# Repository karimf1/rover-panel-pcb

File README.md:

# rover-panel-pcb 

The PCB was missing. It sits on
four standoffs on the panel plate, between the shunt and the signal
connector, and does three jobs:

- **precharge** — it switches the pack through the panel's 22 Ω resistor `R1`
  into the ESC bank, and holds contactor `K1` open until the switched bus
  reaches ~90 % of the pack
- **interlock** — `K1`'s coil is energised through the E-stop loop *and* this
  board, so the board can open `K1` but nothing on it can close `K1` past an
  open E-stop
- **current sense** — an INA228 on the panel's 0.75 mΩ shunt `RS1`, reported
  over I2C

It replaces two of the panel's bought parts — `K2`, an automotive precharge
relay, and `A1`, an INA228 breakout on standoffs — and it answers two of the
panel's open questions: *"precharge is sized by hand and is not in any check"*
and *"is the E-stop hard-wired in series with the contactor coil?"*

The one claim the board is built to prove:

> **K1 cannot close unless the E-stop loop is closed AND the host has raised a
> fresh ARM edge AND the switched bus has reached the precharge threshold** —
> and that is hardware, checked against the exported netlist, not a promise
> made by firmware. There is no firmware.

---

## 1. How the interlock works

The logic is four comparators, one AND gate and one D flip-flop. Every node
that feeds the interlock is an open-collector output pulled up **to EN, not to
5 V** — so the instant the board disarms, every one of them falls with it.

| signal | made by | means |
|---|---|---|
| `ESTOP_OK` | U3C: the *far* side of the E-stop loop (`COIL_POS`) above 13.7 V | the mushroom switch is closed |
| `ARM` | U3D: host line above 1.37 V, 100 k pull-down | the host asked; an unplugged harness reads as *no* |
| `CLR#` | U4: `ARM AND ESTOP_OK` | either one dropping clears the latch immediately |
| `EN` | U5 (74LVC1G74) Q, set only on a **rising edge** of `ARM` delayed 10 ms | armed |
| `CHG` | U3A: switched bus / always-on bus **below** the threshold | precharging |
| `FAULT` | U3B: `CHG` has been high longer than the timer (≥ 1.68 s) | the bus is not charging — latches |
| `K1_G` | `EN`, pulled low by `CHG` (Q2) or `FAULT` (Q3), 1 ms RC | close the contactor |
| `PRE_G` | `EN`, pulled low by `FAULT` (Q4) | precharge switch on |

The flip-flop is there for one reason. With a plain AND gate, releasing the
E-stop while the host is still asserting `ARM` would re-energise the drive
motors on its own. With the latch, **an E-stop release does nothing until the
host drops `ARM` and raises it again.** That is what competition rules mean by
a deliberate restart, and it is scenario 5 in the simulation below.

The K1 coil path is:

```
+24 V -> P1.8 -> J1 -> E-stop -> J1 -> P1.3 -> P1.4 -> K1 coil -> P1.6 -> Q1 -> GND
```

`Q1` is on the low side. It can only *interrupt* that loop.

## 2. The design numbers

### Precharge threshold: a window, not a number

The comparator does not measure "90 % of 24 V". It compares two dividers —
the switched bus against the always-on bus — so it holds from a 21 V cutoff
to a 29.4 V full pack. Its threshold still moves, for three reasons, and
`calcs.pre_ratio_window()` takes every corner of all three:

- the hysteresis resistor injects a fixed 5 V into a divider of a *varying*
  pack, so the trip point shifts with pack voltage
- the four ratio resistors. They are 0.1 % parts because with 1 % parts the highest
  corner trips at 94.75 %, which is **above** the 94.50 % the bus can reach. The
  board would fault on a low pack.
- the LM339's 5 mV offset plus its 250 nA bias current through each divider

```
precharge threshold window     88.34 .. 91.74 % of pack
bus can reach through R1       94.50 % at 21 V, with 50 mA of ESC idle draw
```

**The ESC idle draw is the constraint.** The bus charges towards
`V − I_idle × R1`, not towards `V`. At a 21 V pack and 50 mA of idle current,
R1 takes 1.1 V off the target, and a threshold set at the textbook 95 % would
never be reached — the board would fault on every power-up. The 50 mA is
assumed and is the first thing to measure (§6).

### The fault timer has to outlast a slow precharge

```
precharge time, nominal        0.41 s    (6 mF, 25.9 V)
precharge time, worst          0.73 s    (9 mF, 21 V, highest threshold)
fault timer                    1.68 / 2.36 / 2.66 s   (min / nom / max)
```

The minimum assumes the 10 µF X7R timing capacitor has lost 25 % to tolerance
and DC bias, and that the comparator's full bias current is helping to charge
it. That still leaves 2.3× margin over the slowest legitimate precharge. The
maximum is bounded too: into a dead short, `R1` sees 41 W, inside its 50 W
continuous rating, for as long as the timer takes.

### The panel's supply budget

The panel's `params.py` reserves a supply for the board: a 2 A time-lag fuse on
`DIN2-203`, 18 AWG, 0.2 A continuous and a 2.5 A peak. The panel's
`sizing.py` sizes the wiring from those numbers, and this board checks that
its worst case fits inside them. Neither side can quietly outgrow the other.

```
24 V draw                      76 mA continuous (70 mA of it is K1's hold current)
                               2.17 A worst instant: K1 pull-in while precharge still conducts
```

### Everything else

| check | result |
|---|---|
| INA228 full scale at `ADCRANGE = 0` | 218 A, 0.42 mA per count, `SHUNT_CAL` = 2803 |
| current error at 10 A | 0.31 % (shunt 0.25 %, INA228 gain, offset, filter bias) |
| input TVS SM6T36A | stands off 30.8 V > 29.4 V; clamps 49.9 V < 60 V (every FET on the 24 V side) |
| K1 FET gate drive | 4.85 V on a 5 V −2 % rail, ≥ the 4.5 V its RDS(on) is quoted at |
| K1 coil at pack cutoff | 19.8 V ≥ 16 V pickup, after the E-stop loop, the FET and panel wiring |
| precharge FET gate | zener-clamped, ≤ 12.6 V worst case, from 21 V to 29.4 V (fully on, under ±20 V) |
| every LM339 input | inside `VCC − 1.5 V` at a full pack |
| power traces | 1.0 mm vs 0.70 mm IPC-2221 at 2.5 A as if continuous |

### The behaviour, simulated

`test_calcs.py` finishes with a 1 ms-step simulation of the interlock built
from those same thresholds and time constants — nothing retuned for the test:

```
PASS  power-up, ARM low: nothing switches
PASS  ARM with a healthy bus (3 mF): precharge, then K1, no fault  -- K1 closes 0.20 s after ARM, bus at 90.7 %
PASS  ARM with a healthy bus (9 mF): precharge, then K1, no fault  -- K1 closes 0.58 s after ARM, bus at 90.7 %
PASS  ARM into a shorted bus: FAULT latches, precharge stops, K1 never closes  -- fault 2.36 s after ARM
PASS  E-stop opens while K1 is closed: K1 drops within 1 ms
PASS  E-stop released with ARM still high: K1 stays OPEN (needs a new ARM edge)
PASS  ARM cycled after the E-stop reset: precharge and K1 again
PASS  FAULT holds for as long as ARM stays high (a latch, not a retry loop)
PASS  dropping ARM clears FAULT and leaves everything off
```

## 3. What changed from the plan

1. **It had no latch.** The plan's logic was `ARM AND E-STOP AND PRECHARGED`.
   Writing scenario 4 of the simulation showed what that does: release the
   E-stop with `ARM` still high and the motors come back on by themselves.
   The 74LVC1G74 and its 10 ms clock delay are the fix. KiCad 9 ships no
   74LVC1G74 symbol, so it is generated from a pin map in `spec.py`
   (`hw/gen/gen_lib.py`).
2. **The supply fuse is 2 A, not 1 A.** A 1 A fuse passes the board's 76 mA,
   but K1's 2 A pull-in comes through the same fuse.
3. **No 3.3 V rail.** The plan had an LDO for the INA228. Everything runs at
   5 V instead. The INA228's I2C thresholds do not follow its supply, and
   every output to the host is an open-drain FET, so this 5 V board never
   drives a 3.3 V pin. (That INA228 fact is one of the seven items flagged
   `VERIFY`.)
4. **The board is 110 × 46 mm, not ~90 × 55.** The panel set its height:
   25 mm of signal clearance to `K1` above and to the `DIN2` terminals below
   leaves 46 mm. Width was the only direction left to grow.
5. **The buck's pins are not in the 0.3 mm pack-voltage clearance class.** The
   LM5165's own pins are 0.22 mm apart. A 0.3 mm rule for them fails under the
   footprint itself, so the package sets that spacing.

## 4. The layout

Placement is by hand, in `hw/gen/gen_pcb.py`, because placement *is* the
layout design:

- **P1** (power, coil, E-stop loop) is on the top edge, towards `K1` and `R1`.
  Its edge row is ground plus the E-stop-return/coil+ pair, which never has
  to leave the connector. Every net that travels is on the inner row.
- **P2** (the Kelvin pair) is on the left edge, facing `RS1`. The INA228 is
  turned so its inputs face P2 and its I2C and ground pins face open board.
- **P3** (signal to `J1`) is on the right edge, with the ESD diodes in a
  column in the same order as its pins.
- The coil FET and its clamps are left of P1, the precharge switch and buck
  are right of P1, the comparators are in the middle, and the LEDs are along
  the bottom edge where the hatch is.

The copper between the pads comes from `hw/gen/autoroute.py`: a 0.1 mm grid
A* router, two layers, that runs inside KiCad's own Python using numpy.

- Obstacles are painted at each net's own clearance class. The net being
  routed dilates the map by however much wider it is, so a 1 mm coil trace
  keeps 0.3 mm from everything, and a 0.2 mm signal can still leave a
  0.5 mm-pitch IC.
- Fine-pitch pads get straight escape stubs first, along their own axis.
- If a net cannot get out, it is **promoted** and the whole board re-routes
  from scratch with that net earlier in the queue. That is the cheapest
  rip-up-and-retry there is. The current layout routes on the first attempt
  in about 30 s.
- The ground pour is computed after routing, so a union-find walks every
  island, pad, via and track. Any ground pad the pour does not actually reach
  gets a real track to one it does. An island touching a via is not
  "connected" if that via lands in a fenced-off pocket on the other layer.

None of that is trusted. **kicad-cli DRC with schematic parity is the judge.**

```
802 track segments, 1753 mm of track (181 mm on B.Cu, the ground plane)
205 vias, all tented
0 DRC violations, 0 unconnected pads, 0 footprint errors
```

## 5. Fabrication (Sponsored by PCBWay)

This board was fabricated by PCBWay (https://www.pcbway.com/orderonline.aspx) through their promotional program. Communication was quick: my questions to their representative were answered within one day. Once the order was confirmed I got an email with all the order details, such as tracking number and estimated arrival date. The PCB arrived sealed in a box, packed in foam rubber, so it reached me undamaged. The website is clear and intuitive to use, even for someone placing an order for the first time (like myself). The board itself is excellent. Every dimension matches the design, the exposed copper and pads line up cleanly with no misalignment, and the overall fabrication quality is top-notch.

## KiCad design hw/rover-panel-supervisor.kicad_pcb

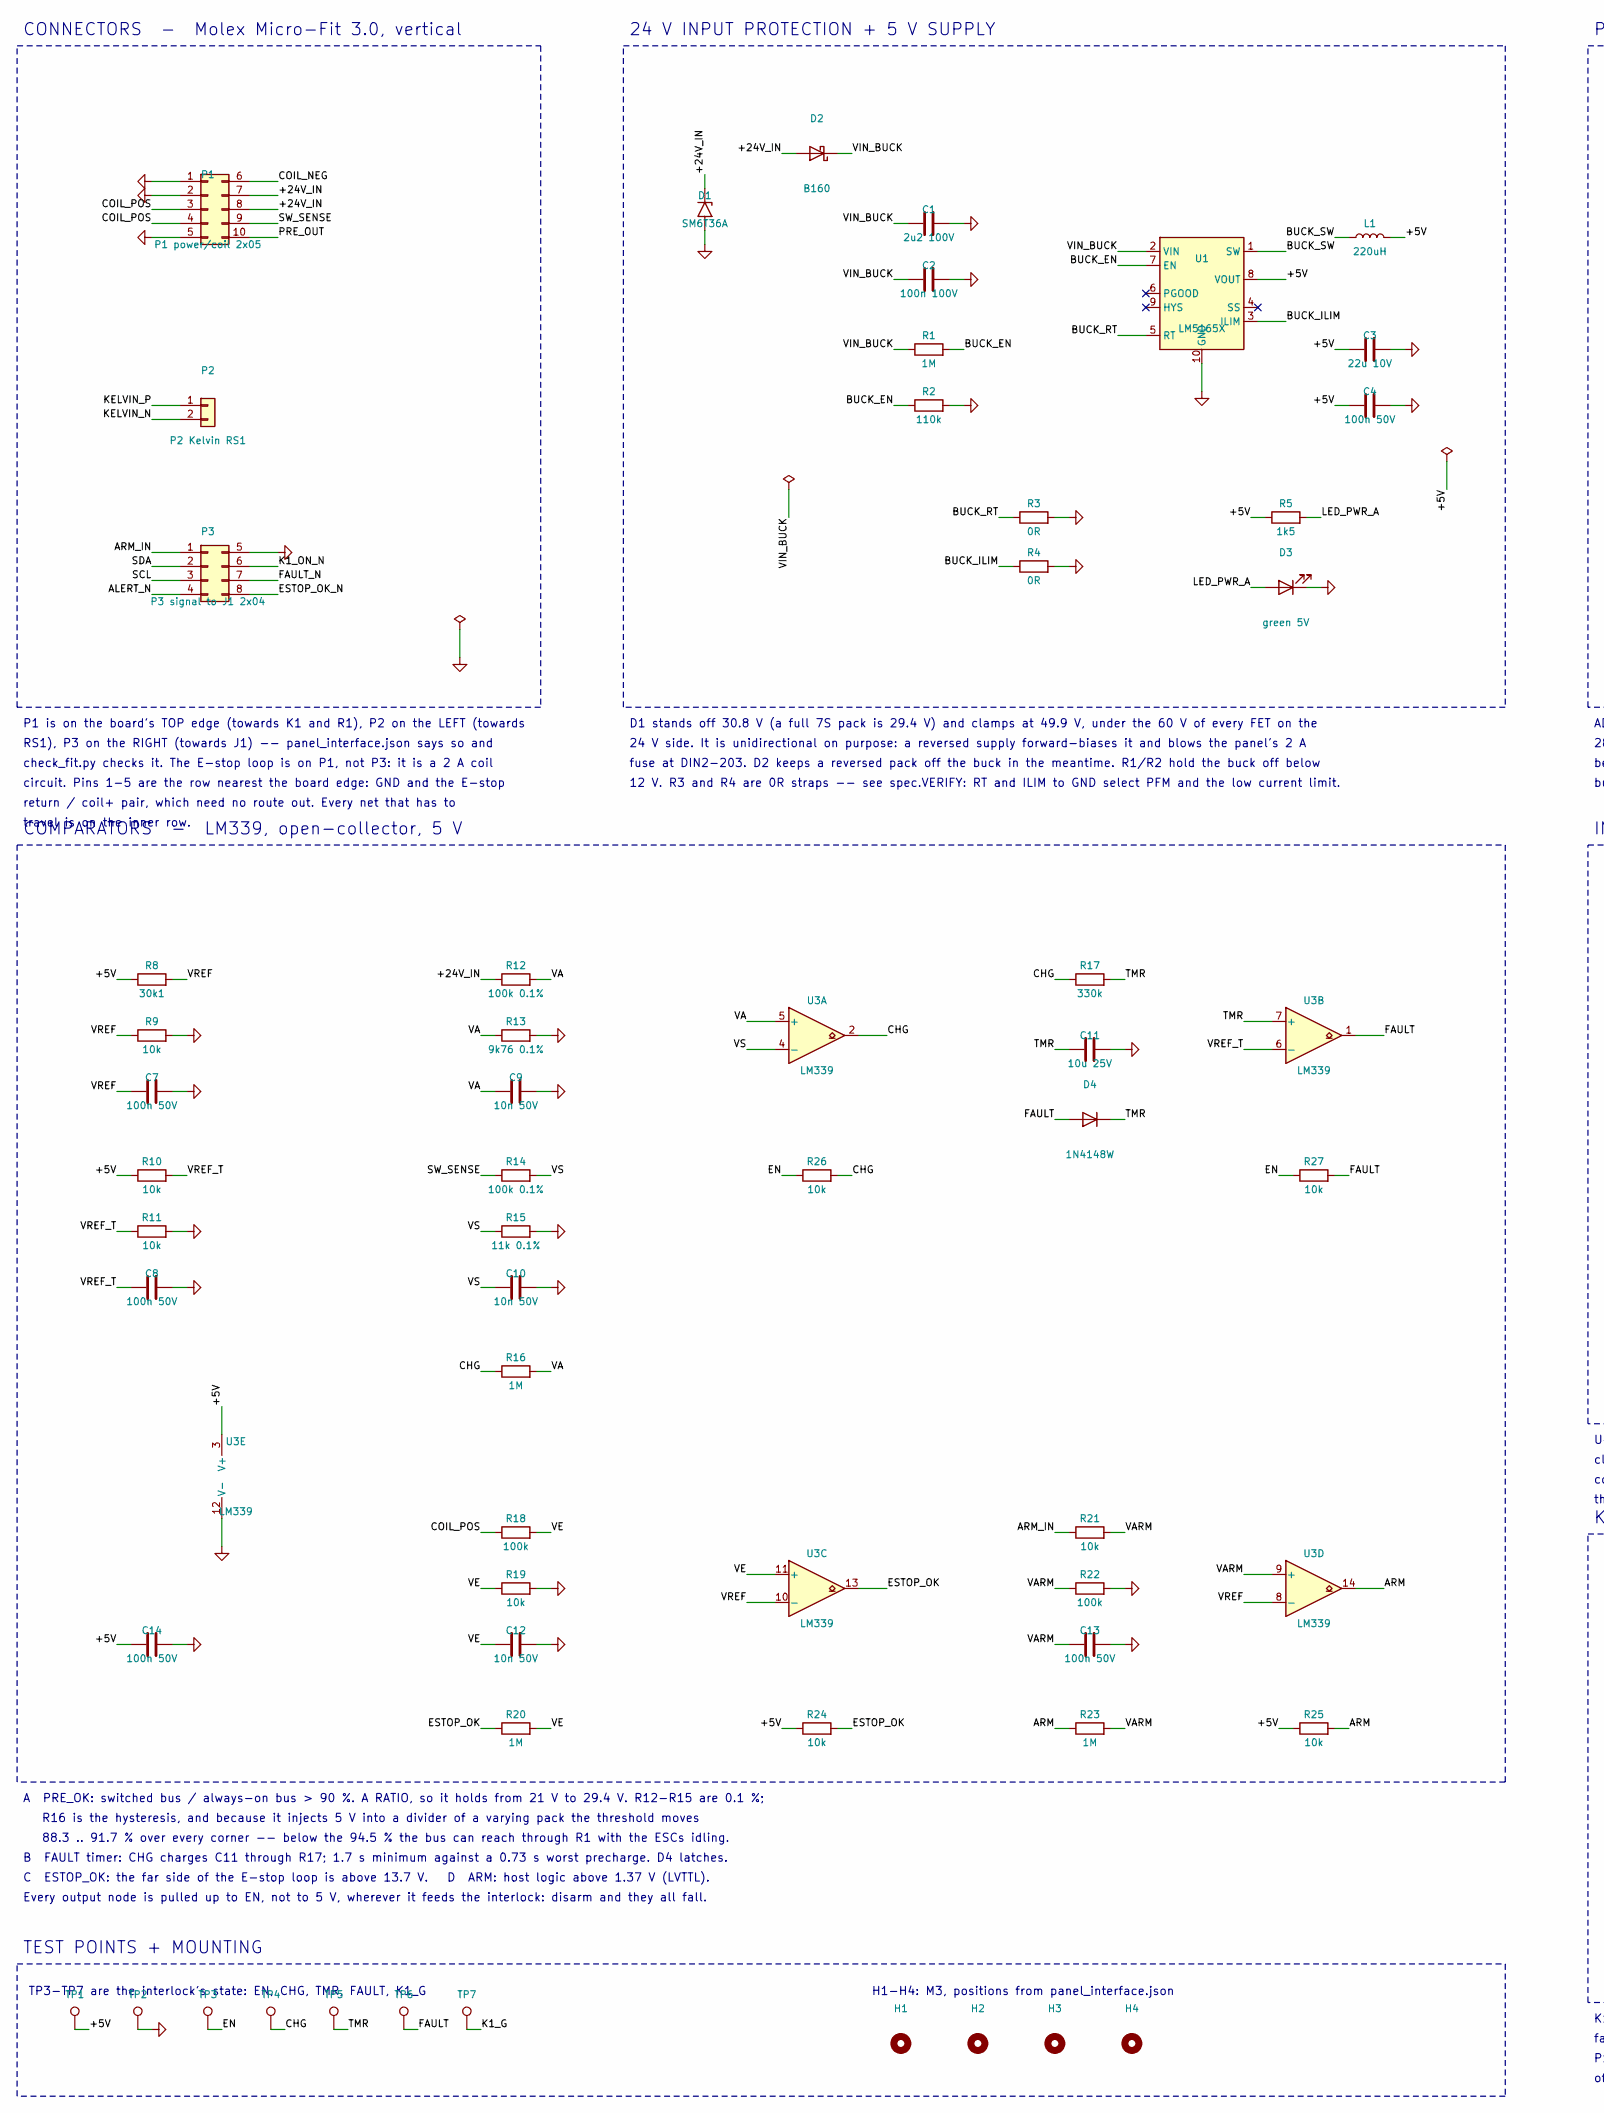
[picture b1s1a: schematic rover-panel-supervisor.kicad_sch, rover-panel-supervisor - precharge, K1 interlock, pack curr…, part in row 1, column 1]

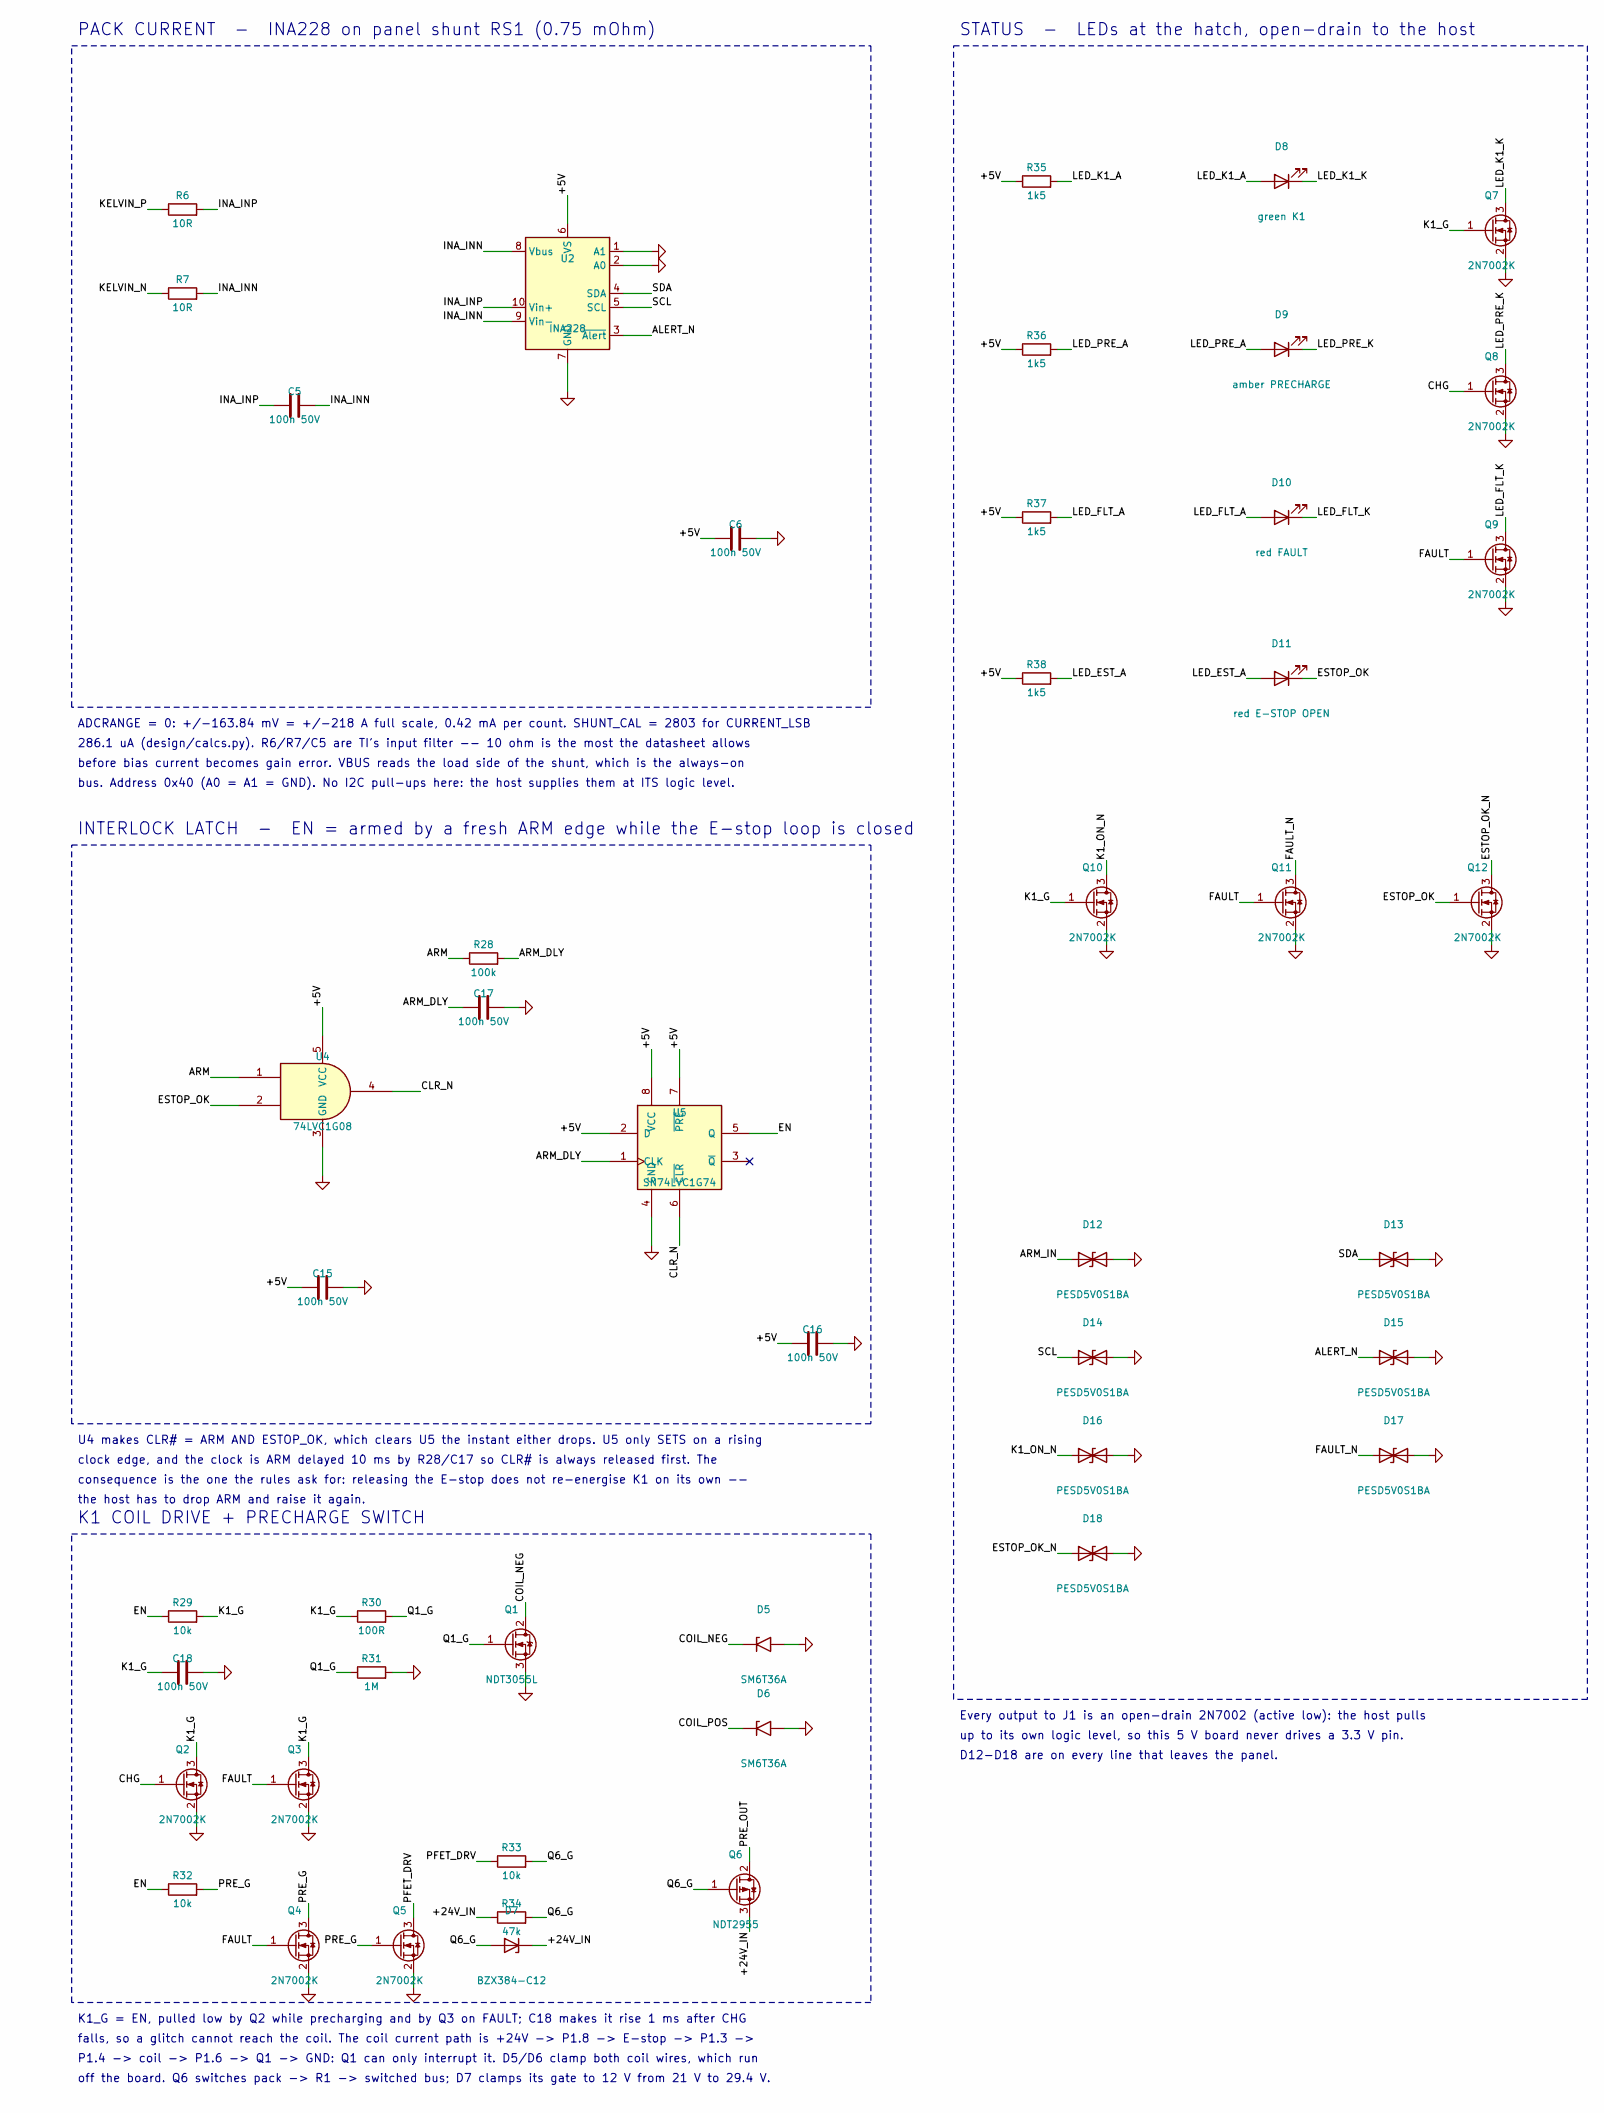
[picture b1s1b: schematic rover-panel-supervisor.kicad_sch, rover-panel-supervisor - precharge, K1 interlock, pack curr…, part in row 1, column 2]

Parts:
C1: 2u2 100V; C_1210_3225Metric; Voltage 100 V
C2: 100n 100V; C_0805_2012Metric; Voltage 100 V
C3: 22u 10V; C_1206_3216Metric; Voltage 10 V
C4, C5, C6, C7, C8, C13, C14, C15, C16, C17, C18: 100n 50V; C_0805_2012Metric; Voltage 50 V
C9, C10, C12: 10n 50V; C_0805_2012Metric; Voltage 50 V
C11: 10u 25V; C_1206_3216Metric; Voltage 25 V
D1: SM6T36A; D_SMB; MPN SM6T36A
D2: B160; D_SMA; MPN B160-13-F
D3: green 5V; LED_0805_2012Metric
D4: 1N4148W; D_SOD-123
D5, D6: SM6T36A; D_SMB
D7: BZX384-C12; D_SOD-323; MPN BZX384-C12
D8: green K1; LED_0805_2012Metric
D9: amber PRECHARGE; LED_0805_2012Metric
D10: red FAULT; LED_0805_2012Metric
D11: red E-STOP OPEN; LED_0805_2012Metric
D12, D13, D14, D15, D16, D17, D18: PESD5V0S1BA; D_SOD-323; MPN PESD5V0S1BA
H1, H2, H3, H4: M3; MountingHole_3.2mm_M3
L1: 220uH; L_Coilcraft_LPS5030; MPN Coilcraft LPS5030-224MRB
P1: P1 power/coil 2x05; Molex_Micro-Fit_3.0_43045-1012_2x05_P3.00mm_Vertical; MPN Molex 43045-1012
P2: P2 Kelvin RS1; Molex_Micro-Fit_3.0_43045-0212_2x01_P3.00mm_Vertical; MPN Molex 43045-0212
P3: P3 signal to J1 2x04; Molex_Micro-Fit_3.0_43045-0812_2x04_P3.00mm_Vertical; MPN Molex 43045-0812
Q1: NDT3055L; SOT-223-3_TabPin2; MPN NDT3055L
Q2, Q3, Q4, Q5, Q7, Q8, Q9, Q10, Q11, Q12: 2N7002K; SOT-23; MPN 2N7002K
Q6: NDT2955; SOT-223-3_TabPin2; MPN NDT2955
R1, R16, R20, R23, R31: 1M; R_0805_2012Metric
R2: 110k; R_0805_2012Metric
R3, R4: 0R; R_0805_2012Metric
R5, R35, R36, R37, R38: 1k5; R_0805_2012Metric
R6, R7: 10R; R_0805_2012Metric
R8: 30k1; R_0805_2012Metric
R9, R10, R11, R19, R21, R24, R25, R26, R27, R29, R32, R33: 10k; R_0805_2012Metric
R12, R14: 100k 0.1%; R_0805_2012Metric; Tolerance 0.1%
R13: 9k76 0.1%; R_0805_2012Metric; Tolerance 0.1%
R15: 11k 0.1%; R_0805_2012Metric; Tolerance 0.1%
R17: 330k; R_0805_2012Metric
R18, R22, R28: 100k; R_0805_2012Metric
R30: 100R; R_0805_2012Metric
R34: 47k; R_0805_2012Metric
TP1: +5V; TestPoint_Pad_D1.5mm
TP2: GND; TestPoint_Pad_D1.5mm
TP3: EN; TestPoint_Pad_D1.5mm
TP4: CHG; TestPoint_Pad_D1.5mm
TP5: TMR; TestPoint_Pad_D1.5mm
TP6: FAULT; TestPoint_Pad_D1.5mm
TP7: K1_G; TestPoint_Pad_D1.5mm
U1: LM5165X; Texas_S-PVSON-N10_ThermalVias; MPN LM5165XDRCR
U2: INA228; VSSOP-10_3x3mm_P0.5mm; MPN INA228AIDGSR
U3: LM339; SOIC-14_3.9x8.7mm_P1.27mm; MPN LM339DR
U4: 74LVC1G08; SOT-23-5; MPN SN74LVC1G08DBVR
U5: SN74LVC1G74; SSOP-8_2.95x2.8mm_P0.65mm

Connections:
/+5V: C3.1, C4.1, C6.1, C14.1, C15.1, C16.1, L1.2, R5.1, R8.1, R10.1, R24.1, R25.1, R35.1, R36.1, R37.1, R38.1, TP1.1, U1.8 (VOUT), U2.6 (VS), U3.3 (V+), U4.5 (VCC), U5.2 (D), U5.7 (~PRE), U5.8 (VCC)
/+24V_IN: D1.1 (A1), D2.2 (A), D7.1 (K), P1.7, P1.8, Q6.3 (S), R12.1, R34.1
/ALERT_N: D15.1 (A1), P3.4, U2.3 (~Alert)
/ARM: R23.1, R25.2, R28.1, U3.14, U4.1
/ARM_DLY: C17.1, R28.2, U5.1 (CLK)
/ARM_IN: D12.1 (A1), P3.1, R21.1
/BUCK_EN: R1.2, R2.1, U1.7 (EN)
/BUCK_ILIM: R4.1, U1.3 (ILIM)
/BUCK_RT: R3.1, U1.5 (RT)
/BUCK_SW: L1.1, U1.1 (SW)
/CHG: Q2.1 (G), Q8.1 (G), R16.1, R17.1, R26.2, TP4.1, U3.2
/CLR_N: U4.4, U5.6 (~CLR)
/COIL_NEG: D5.1 (A1), P1.6, Q1.2 (D)
/COIL_POS: D6.1 (A1), P1.3, P1.4, R18.1
/EN: R26.1, R27.1, R29.1, R32.1, TP3.1, U5.5 (Q)
/ESTOP_OK: D11.1 (K), Q12.1 (G), R20.1, R24.2, U3.13, U4.2
/ESTOP_OK_N: D18.1 (A1), P3.8, Q12.3 (D)
/FAULT: D4.2 (A), Q3.1 (G), Q4.1 (G), Q9.1 (G), Q11.1 (G), R27.2, TP6.1, U3.1
/FAULT_N: D17.1 (A1), P3.7, Q11.3 (D)
/INA_INN: C5.2, R7.2, U2.8 (Vbus), U2.9 (Vin-)
/INA_INP: C5.1, R6.2, U2.10 (Vin+)
/K1_G: C18.1, Q2.3 (D), Q3.3 (D), Q7.1 (G), Q10.1 (G), R29.2, R30.1, TP7.1
/K1_ON_N: D16.1 (A1), P3.6, Q10.3 (D)
/KELVIN_N: P2.2, R7.1
/KELVIN_P: P2.1, R6.1
/LED_EST_A: D11.2 (A), R38.2
/LED_FLT_A: D10.2 (A), R37.2
/LED_FLT_K: D10.1 (K), Q9.3 (D)
/LED_K1_A: D8.2 (A), R35.2
/LED_K1_K: D8.1 (K), Q7.3 (D)
/LED_PRE_A: D9.2 (A), R36.2
/LED_PRE_K: D9.1 (K), Q8.3 (D)
/LED_PWR_A: D3.2 (A), R5.2
/PFET_DRV: Q5.3 (D), R33.1
/PRE_G: Q4.3 (D), Q5.1 (G), R32.2
/PRE_OUT: P1.10, Q6.2 (D)
/Q1_G: Q1.1 (G), R30.2, R31.1
/Q6_G: D7.2 (A), Q6.1 (G), R33.2, R34.2
/SCL: D14.1 (A1), P3.3, U2.5 (SCL)
/SDA: D13.1 (A1), P3.2, U2.4 (SDA)
/SW_SENSE: P1.9, R14.1
/TMR: C11.1, D4.1 (K), R17.2, TP5.1, U3.7 (+)
/VA: C9.1, R12.2, R13.1, R16.2, U3.5 (+)
/VARM: C13.1, R21.2, R22.1, R23.2, U3.9 (+)
/VE: C12.1, R18.2, R19.1, R20.2, U3.11 (+)
/VIN_BUCK: C1.1, C2.1, D2.1 (K), R1.1, U1.2 (VIN)
/VREF: C7.1, R8.2, R9.1, U3.8 (-), U3.10 (-)
/VREF_T: C8.1, R10.2, R11.1, U3.6 (-)
/VS: C10.1, R14.2, R15.1, U3.4 (-)
GND: C1.2, C2.2, C3.2, C4.2, C6.2, C7.2, C8.2, C9.2, C10.2, C11.2, C12.2, C13.2, C14.2, C15.2, C16.2, C17.2, C18.2, D1.2 (A2), D3.1 (K), D5.2 (A2), D6.2 (A2), D12.2 (A2), D13.2 (A2), D14.2 (A2), D15.2 (A2), D16.2 (A2), D17.2 (A2), D18.2 (A2), P1.1, P1.2, P1.5, P3.5, Q1.3 (S), Q2.2 (S), Q3.2 (S), Q4.2 (S), Q5.2 (S), Q7.2 (S), Q8.2 (S), Q9.2 (S), Q10.2 (S), Q11.2 (S), Q12.2 (S), R2.2, R3.2, R4.2, R9.2, R11.2, R13.2, R15.2, R19.2, R22.2, R31.2, TP2.1, U1.10 (GND), U1.11 (GND), U2.1 (A1), U2.2 (A0), U2.7 (GND), U3.12 (V-), U4.3 (GND), U5.4 (GND)

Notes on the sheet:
CONNECTORS - Molex Micro-Fit 3.0, vertical
P1 is on the board's TOP edge (towards K1 and R1), P2 on the LEFT (towards
RS1), P3 on the RIGHT (towards J1) -- panel_interface.json says so and
check_fit.py checks it. The E-stop loop is on P1, not P3: it is a 2 A coil
circuit. Pins 1-5 are the row nearest the board edge: GND and the E-stop
return / coil+ pair, which need no route out. Every net that has to
travel is on the inner row.
24 V INPUT PROTECTION + 5 V SUPPLY
D1 stands off 30.8 V (a full 7S pack is 29.4 V) and clamps at 49.9 V, under the 60 V of every FET on the
24 V side. It is unidirectional on purpose: a reversed supply forward-biases it and blows the panel's 2 A
fuse at DIN2-203. D2 keeps a reversed pack off the buck in the meantime. R1/R2 hold the buck off below
12 V. R3 and R4 are 0R straps -- see spec.VERIFY: RT and ILIM to GND select PFM and the low current limit.
PACK CURRENT - INA228 on panel shunt RS1 (0.75 mOhm)
ADCRANGE = 0: +/-163.84 mV = +/-218 A full scale, 0.42 mA per count. SHUNT_CAL = 2803 for CURRENT_LSB
286.1 uA (design/calcs.py). R6/R7/C5 are TI's input filter -- 10 ohm is the most the datasheet allows
before bias current becomes gain error. VBUS reads the load side of the shunt, which is the always-on
bus. Address 0x40 (A0 = A1 = GND). No I2C pull-ups here: the host supplies them at ITS logic level.
COMPARATORS - LM339, open-collector, 5 V
A PRE_OK: switched bus / always-on bus > 90 %. A RATIO, so it holds from 21 V to 29.4 V. R12-R15 are 0.1 %;
R16 is the hysteresis, and because it injects 5 V into a divider of a varying pack the threshold moves
88.3 .. 91.7 % over every corner -- below the 94.5 % the bus can reach through R1 with the ESCs idling.
B FAULT timer: CHG charges C11 through R17; 1.7 s minimum against a 0.73 s worst precharge. D4 latches.
C ESTOP_OK: the far side of the E-stop loop is above 13.7 V. D ARM: host logic above 1.37 V (LVTTL).
Every output node is pulled up to EN, not to 5 V, wherever it feeds the interlock: disarm and they all fall.
INTERLOCK LATCH - EN = armed by a fresh ARM edge while the E-stop loop is closed
U4 makes CLR# = ARM AND ESTOP_OK, which clears U5 the instant either drops. U5 only SETS on a rising
clock edge, and the clock is ARM delayed 10 ms by R28/C17 so CLR# is always released first. The
consequence is the one the rules ask for: releasing the E-stop does not re-energise K1 on its own --
the host has to drop ARM and raise it again.
K1 COIL DRIVE + PRECHARGE SWITCH
K1_G = EN, pulled low by Q2 while precharging and by Q3 on FAULT; C18 makes it rise 1 ms after CHG
falls, so a glitch cannot reach the coil. The coil current path is +24V -> P1.8 -> E-stop -> P1.3 ->
P1.4 -> coil -> P1.6 -> Q1 -> GND: Q1 can only interrupt it. D5/D6 clamp both coil wires, which run
off the board. Q6 switches pack -> R1 -> switched bus; D7 clamps its gate to 12 V from 21 V to 29.4 V.
STATUS - LEDs at the hatch, open-drain to the host
Every output to J1 is an open-drain 2N7002 (active low): the host pulls
up to its own logic level, so this 5 V board never drives a 3.3 V pin.
D12-D18 are on every line that leaves the panel.
TEST POINTS + MOUNTING
TP3-TP7 are the interlock's state: EN, CHG, TMR, FAULT, K1_G

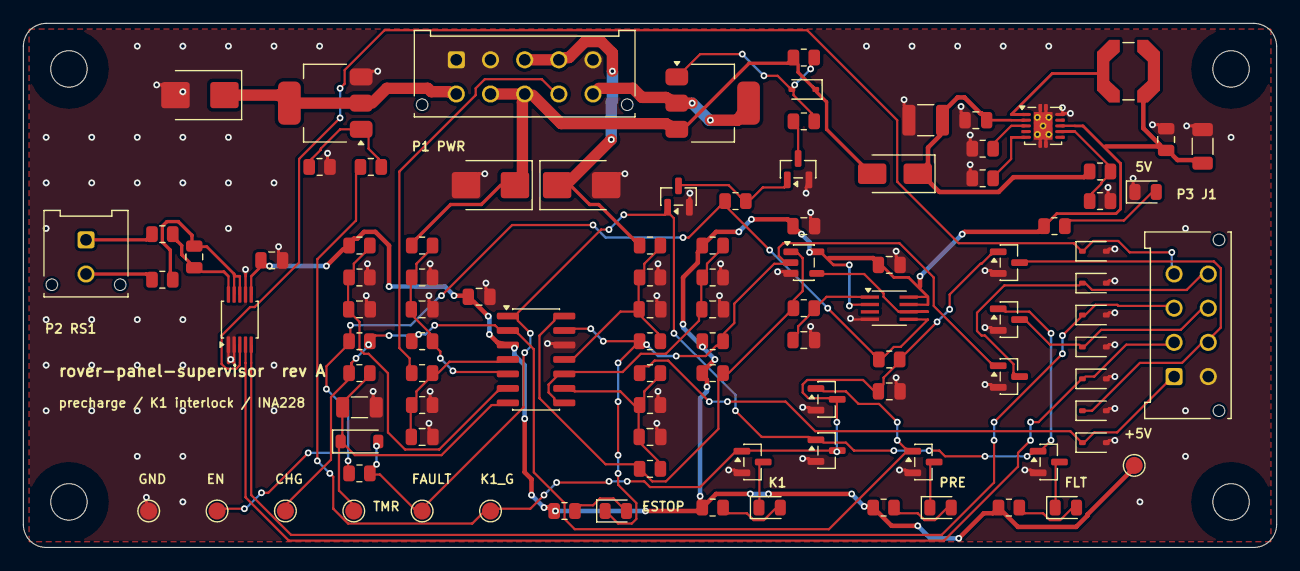
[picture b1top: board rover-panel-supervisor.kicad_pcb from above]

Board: 2 copper layers, 110.0 x 46.0 mm, 106 parts (0 on the bottom side), 50 nets.

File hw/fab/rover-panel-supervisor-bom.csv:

"Refs","Value","Footprint","MPN","Qty","DNP"
"C1","2u2 100V","Capacitor_SMD:C_1210_3225Metric","","1",""
"C2","100n 100V","Capacitor_SMD:C_0805_2012Metric","","1",""
"C3","22u 10V","Capacitor_SMD:C_1206_3216Metric","","1",""
"C4-C8,C13-C18","100n 50V","Capacitor_SMD:C_0805_2012Metric","","11",""
"C9,C10,C12","10n 50V","Capacitor_SMD:C_0805_2012Metric","","3",""
"C11","10u 25V","Capacitor_SMD:C_1206_3216Metric","","1",""
"D1,D5,D6","SM6T36A","Diode_SMD:D_SMB","SM6T36A","3",""
"D2","B160","Diode_SMD:D_SMA","B160-13-F","1",""
"D3","green 5V","LED_SMD:LED_0805_2012Metric","","1",""
"D4","1N4148W","Diode_SMD:D_SOD-123","","1",""
"D7","BZX384-C12","Diode_SMD:D_SOD-323","BZX384-C12","1",""
"D8","green K1","LED_SMD:LED_0805_2012Metric","","1",""
"D9","amber PRECHARGE","LED_SMD:LED_0805_2012Metric","","1",""
"D10","red FAULT","LED_SMD:LED_0805_2012Metric","","1",""
"D11","red E-STOP OPEN","LED_SMD:LED_0805_2012Metric","","1",""
"D12-D18","PESD5V0S1BA","Diode_SMD:D_SOD-323","PESD5V0S1BA","7",""
"L1","220uH","Inductor_SMD:L_Coilcraft_LPS5030","Coilcraft LPS5030-224MRB","1",""
"P1","P1 power/coil 2x05","Connector_Molex:Molex_Micro-Fit_3.0_43045-1012_2x05_P3.00mm_Vertical","Molex 43045-1012","1",""
"P2","P2 Kelvin RS1","Connector_Molex:Molex_Micro-Fit_3.0_43045-0212_2x01_P3.00mm_Vertical","Molex 43045-0212","1",""
"P3","P3 signal to J1 2x04","Connector_Molex:Molex_Micro-Fit_3.0_43045-0812_2x04_P3.00mm_Vertical","Molex 43045-0812","1",""
"Q1","NDT3055L","Package_TO_SOT_SMD:SOT-223-3_TabPin2","NDT3055L","1",""
"Q2-Q5,Q7-Q12","2N7002K","Package_TO_SOT_SMD:SOT-23","2N7002K","10",""
"Q6","NDT2955","Package_TO_SOT_SMD:SOT-223-3_TabPin2","NDT2955","1",""
"R1,R16,R20,R23,R31","1M","Resistor_SMD:R_0805_2012Metric","","5",""
"R2","110k","Resistor_SMD:R_0805_2012Metric","","1",""
"R3,R4","0R","Resistor_SMD:R_0805_2012Metric","","2",""
"R5,R35-R38","1k5","Resistor_SMD:R_0805_2012Metric","","5",""
"R6,R7","10R","Resistor_SMD:R_0805_2012Metric","","2",""
"R8","30k1","Resistor_SMD:R_0805_2012Metric","","1",""
"R9-R11,R19,R21,R24-R27,R29,R32,R33","10k","Resistor_SMD:R_0805_2012Metric","","12",""
"R12,R14","100k 0.1%","Resistor_SMD:R_0805_2012Metric","","2",""
"R13","9k76 0.1%","Resistor_SMD:R_0805_2012Metric","","1",""
"R15","11k 0.1%","Resistor_SMD:R_0805_2012Metric","","1",""
"R17","330k","Resistor_SMD:R_0805_2012Metric","","1",""
"R18,R22,R28","100k","Resistor_SMD:R_0805_2012Metric","","3",""
"R30","100R","Resistor_SMD:R_0805_2012Metric","","1",""
"R34","47k","Resistor_SMD:R_0805_2012Metric","","1",""
"U1","LM5165X","Package_SON:Texas_S-PVSON-N10_ThermalVias","LM5165XDRCR","1",""
"U2","INA228","Package_SO:VSSOP-10_3x3mm_P0.5mm","INA228AIDGSR","1",""
"U3","LM339","Package_SO:SOIC-14_3.9x8.7mm_P1.27mm","LM339DR","1",""
"U4","74LVC1G08","Package_TO_SOT_SMD:SOT-23-5","SN74LVC1G08DBVR","1",""
"U5","SN74LVC1G74","Package_SO:SSOP-8_2.95x2.8mm_P0.65mm","","1",""

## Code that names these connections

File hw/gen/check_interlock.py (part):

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    if k == "CONN":
        continue
    if k == "TVS":
        other = [PIN[(r, p)] for (rr, p) in PIN if rr == r and PIN[(rr, p)] != "COIL_POS"]
        ok &= other == ["GND"]
        why.append(f"{r} TVS to {other}")
    elif k == "R":
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        why.append(f"{r} UNEXPECTED")
check("COIL_POS touches only P1, a clamp to GND and a >= 100 k sense resistor",
      ok, ", ".join(why))
check("COIL_POS arrives on two P1 pins: E-stop return in, coil + out",
      sorted(p for r, p in on("COIL_POS") if r == "P1") == ["3", "4"])
check("the E-stop loop source is +24V_IN on P1.8",
      PIN.get(("P1", "8")) == "+24V_IN")
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check("Q1's source is GND", PIN[("Q1", q1["S"])] == "GND")
check("Q1's gate is driven only through R30 from K1_G (R31 pulls it down)",
      sorted(r for r, _ in on(PIN[("Q1", q1["G"])])) == ["Q1", "R30", "R31"]
      and {PIN[("R30", "1")], PIN[("R30", "2")]} == {"K1_G", "Q1_G"}
      and {PIN[("R31", "1")], PIN[("R31", "2")]} == {"Q1_G", "GND"})

# ------------------------------------------------ 3. what can pull K1_G high
pullers, holders, loads = [], [], []
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check("U5 D and /PRE are tied high: it can only SET on a clock edge",
      PIN[("U5", "2")] == "+5V" and PIN[("U5", "7")] == "+5V")
check("U5 /CLR = U4 output = ARM AND ESTOP_OK",
      PIN[("U5", "6")] == "CLR_N" and sorted(on("CLR_N")) == [("U4", "4"), ("U5", "6")]
      and {PIN[("U4", "1")], PIN[("U4", "2")]} == {"ARM", "ESTOP_OK"})
check("U5 is clocked by ARM delayed through R28/C17",
      PIN[("U5", "1")] == "ARM_DLY"
      and {PIN[("R28", "1")], PIN[("R28", "2")]} == {"ARM", "ARM_DLY"})

# ------------------------------------------------ 5. the comparators read what they claim
# LM339 SOIC-14:  A (+5 -4 out 2)  B (+7 -6 out 1)  C (+11 -10 out 13)  D (+9 -8 out 14)
check("ESTOP_OK compares VE (+11) against VREF (-10) on output 13",
      (PIN[("U3", "13")], PIN[("U3", "11")], PIN[("U3", "10")]) == ("ESTOP_OK", "VE", "VREF"))
check("VE is a divider off COIL_POS -- the FAR side of the E-stop loop",
      {PIN[("R18", "1")], PIN[("R18", "2")]} == {"COIL_POS", "VE"}
      and {PIN[("R19", "1")], PIN[("R19", "2")]} == {"VE", "GND"})
check("CHG compares VA (+5, always-on bus) against VS (-4, switched bus) on output 2",
      (PIN[("U3", "2")], PIN[("U3", "5")], PIN[("U3", "4")]) == ("CHG", "VA", "VS"))
check("VA divides +24V_IN and VS divides SW_SENSE",
      {PIN[("R12", "1")], PIN[("R12", "2")]} == {"+24V_IN", "VA"}
      and {PIN[("R14", "1")], PIN[("R14", "2")]} == {"SW_SENSE", "VS"})
check("SW_SENSE comes in on P1.9 and PRE_OUT leaves on P1.10",
      PIN[("P1", "9")] == "SW_SENSE" and PIN[("P1", "10")] == "PRE_OUT")
check("FAULT is the timer comparator (TMR +7 vs VREF_T -6, output 1)",
      (PIN[("U3", "1")], PIN[("U3", "7")], PIN[("U3", "6")]) == ("FAULT", "TMR", "VREF_T"))
check("ARM is the receiver comparator (VARM +9 vs VREF -8, output 14)",
      (PIN[("U3", "14")], PIN[("U3", "9")], PIN[("U3", "8")]) == ("ARM", "VARM", "VREF"))
check("an unplugged harness reads as disarmed (R22 pulls VARM to GND)",
      {PIN[("R22", "1")], PIN[("R22", "2")]} == {"VARM", "GND"})

# ------------------------------------------------ 6. the precharge switch
q6 = fet_pins("Q6")
check("Q6 switches +24V_IN to PRE_OUT",
      PIN[("Q6", q6["S"])] == "+24V_IN" and PIN[("Q6", q6["D"])] == "PRE_OUT")
pg_up = [r for r, p in on("PRE_G") if kind(r) == "R"]
check("PRE_G is raised only by R32 from EN, and dropped by FAULT through Q4",
      pg_up == ["R32"] and PIN[("R32", "1")] == "EN"
      and PIN[("Q4", fet_pins("Q4")["G"])] == "FAULT"
      and PIN[("Q4", fet_pins("Q4")["D"])] == "PRE_G")

print()
if FAILED:
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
